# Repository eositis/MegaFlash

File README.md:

# MegaFlash for Apple IIc/IIc+

MegaFlash is an internal storage device for Apple IIc/IIc plus computer.

## Feature List

- 128MB/256MB Capacity, divided into 4/8 ProDOS Drives
- 256kB RAM Disk on Pico 2 (RP2350); 140kB on Pico W (RP2040)
- ROM Disk for Disaster Recovery
- 256kB Slinky Emulation on stock firmware
- Boot Menu (Similar to ROM4X/5X)
- Control Panel
- Real Time Clock with ProDOS clock driver
- Network Time Sync (NTP Client)
- Upload/Download ProDOS Image file via WIFI and TFTP Server
- Upload/Download ProDOS Image file via XModem and USB serial port
- FPU for Applesoft BASIC
- Bug fixes of System ROM and Applesoft

A brief [user guide](https://github.com/eositis/MegaFlash/blob/main/MegaFlash%20for%20a2s4000%20installation%20guide.pdf) is available for more information.

## Requirement
- Apple IIc computer with Memory Expansion Card connector or
- Apple IIc plus computer

System ROM replacement is required for MegaFlash to function.

## Hardware
The hardware is quite simple.  All the hard work is handled by Pi Pico.  Apple 65C02 CPU only needs to copy data between RAM and Pico. Schematic is available [here](./kicad/rev1.0/schematic-rev1.0.pdf).

- Raspberry Pi Pico2 W
- Winbond 25Q01 NOR Flash memory
- GAL16V8 PLD for address decode
- 5V to 3.3V Logic Level Shifter

## Project Directories

There are 3 software projects. There is not enough space in Apple ROM to store the Control Panel program.  The program is stored in Pico flash memory. 

`firmware` Project Directory of Apple ROM Patches\
`cpanel` Control Panel project\
`pico` Raspberry Pi Pico firmware\
`common` Common header files used by all 3 projects

## Sponsorship

MegaFlash development for commercial sale has been partly sponsored by PCBway. Preparing products for commercial release is expensive, often requiring board respins to resolve manufacturing and logistics issues. PCBway production and delivery are fast and efficient, helping compress the go-to market timeline. Many thanks!

<a href="https://www.pcbway.com">
  <p align="center">
  
</a>

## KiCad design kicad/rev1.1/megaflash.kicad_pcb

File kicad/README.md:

# MegaFlash PCB

Currently, there are two PCB revisions, 1.0 and 1.1. They are functionally identical. 

Rev 1.0 board is more compact. It is optimized for machine assembly.

Rev 1.1 board is bigger. It is designed for hand assembly.  The components are either through hole or 1.27mm pitch SOICs.

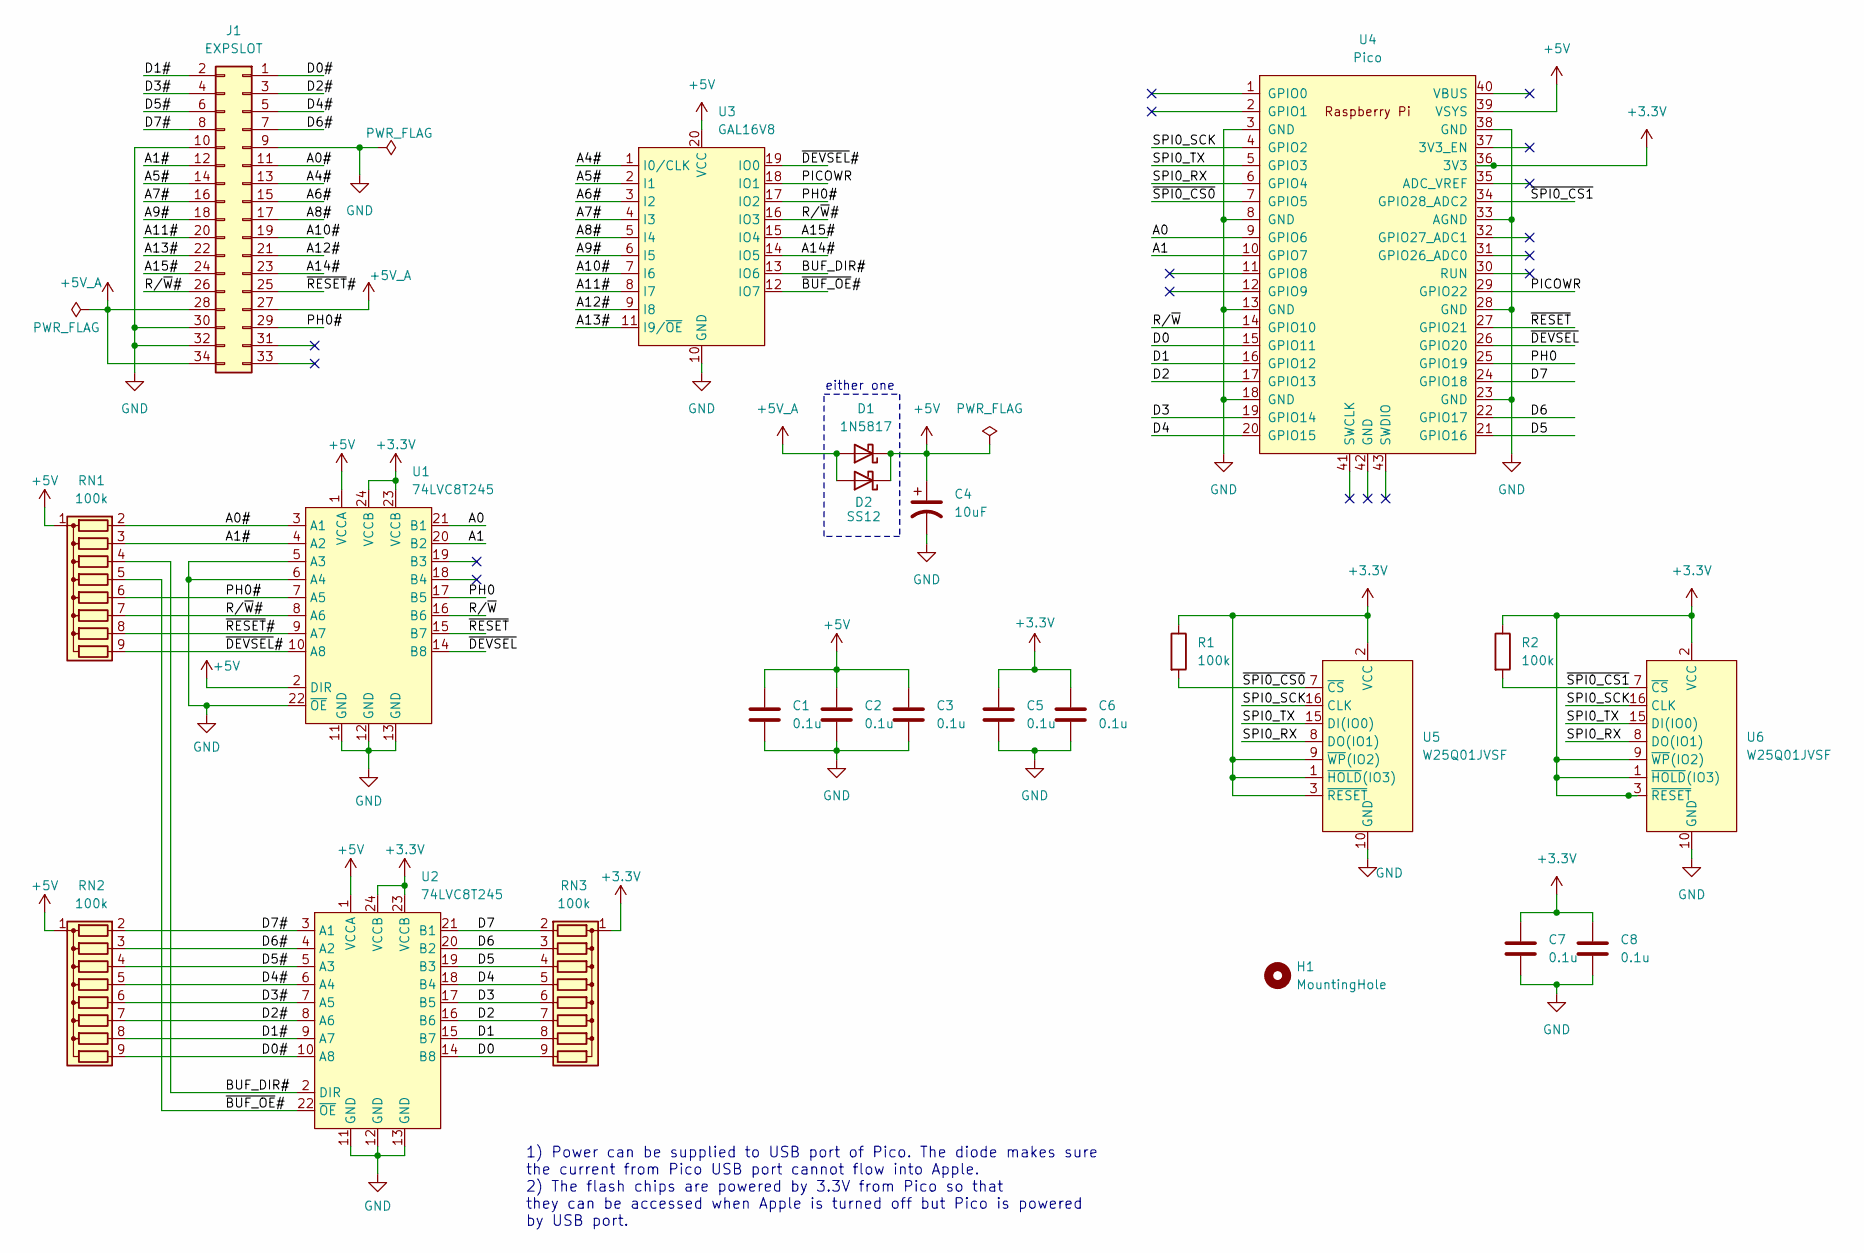
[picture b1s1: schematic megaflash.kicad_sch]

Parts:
C1, C2, C3, C5, C6, C7, C8: 0.1u; C_Disc_D5.1mm_W3.2mm_P5.00mm; Mouser Part No 594-K104K15X7RF5WH5
C4: 10uF; CP_Radial_D5.0mm_P2.00mm; Mouser Part No 710-860010372001
D1: 1N5817; D_DO-41_SOD81_P10.16mm_Horizontal; Mouser Part No 625-1N5817-E3/53
D2: SS12; D_SMA; Mouser Part No 625-SS12-E3
H1: MountingHole; MountingHole_2.7mm_M2.5
J1: EXPSLOT; PinHeader_2x17_P2.54mm_Vertical_Mirror; Mouser Part No 200-TSW11715GD
R1, R2: 100k; R_Axial_DIN0207_L6.3mm_D2.5mm_P10.16mm_Horizontal
RN1, RN2, RN3: 100k; R_Array_SIP9; Mouser Part No 652-4609X-1LF-100K
U1, U2: 74LVC8T245; SOIC-24W_7.5x15.4mm_P1.27mm; Mfr Part No SN74LVC8T245DWR; Mouser Part No 595-SN74LVC8T245DWR
U3: GAL16V8; DIP-20_W7.62mm_LongPads
U4: Pico; RPi_Pico_SMD_NO_LABEL_NO_DEBUG
U5, U6: W25Q01JVSF; SOIC-16W_7.5x10.3mm_P1.27mm; Mouser Part No 454-W25Q01JVSFIM

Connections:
+3.3V: C5.1, C6.1, C7.1, C8.1, R1.1, R2.1, RN3.1 (common), U1.23 (VCCB), U1.24 (VCCB), U2.23 (VCCB), U2.24 (VCCB), U4.36 (3V3), U5.1 (~HOLD(IO3)), U5.2 (VCC), U5.3 (~RESET), U5.9 (~WP(IO2)), U6.1 (~HOLD(IO3)), U6.2 (VCC), U6.3 (~RESET), U6.9 (~WP(IO2))
+5V: C1.1, C2.1, C3.1, C4.1, D1.1 (K), D2.1 (K), RN1.1 (common), RN2.1 (common), U1.1 (VCCA), U1.2 (DIR), U2.1 (VCCA), U3.20 (VCC), U4.39 (VSYS)
+5V_A: D1.2 (A), D2.2 (A), J1.27, J1.28, J1.34
/A0: U1.21 (B1), U4.9 (GPIO6)
/A0#: J1.11, RN1.2 (R1), U1.3 (A1)
/A1: U1.20 (B2), U4.10 (GPIO7)
/A1#: J1.12, RN1.3 (R2), U1.4 (A2)
/A4#: J1.13, U3.1 (I0/CLK)
/A5#: J1.14, U3.2 (I1)
/A6#: J1.15, U3.3 (I2)
/A7#: J1.16, U3.4 (I3)
/A8#: J1.17, U3.5 (I4)
/A9#: J1.18, U3.6 (I5)
/A10#: J1.19, U3.7 (I6)
/A11#: J1.20, U3.8 (I7)
/A12#: J1.21, U3.9 (I8)
/A13#: J1.22, U3.11 (I9/~OE)
/A14#: J1.23, U3.14 (IO5)
/A15#: J1.24, U3.15 (IO4)
/BUF_DIR#: RN1.4 (R3), U2.2 (DIR), U3.13 (IO6)
/D0: RN3.9 (R8), U2.14 (B8), U4.15 (GPIO11)
/D0#: J1.1, RN2.9 (R8), U2.10 (A8)
/D1: RN3.8 (R7), U2.15 (B7), U4.16 (GPIO12)
/D1#: J1.2, RN2.8 (R7), U2.9 (A7)
/D2: RN3.7 (R6), U2.16 (B6), U4.17 (GPIO13)
/D2#: J1.3, RN2.7 (R6), U2.8 (A6)
/D3: RN3.6 (R5), U2.17 (B5), U4.19 (GPIO14)
/D3#: J1.4, RN2.6 (R5), U2.7 (A5)
/D4: RN3.5 (R4), U2.18 (B4), U4.20 (GPIO15)
/D4#: J1.5, RN2.5 (R4), U2.6 (A4)
/D5: RN3.4 (R3), U2.19 (B3), U4.21 (GPIO16)
/D5#: J1.6, RN2.4 (R3), U2.5 (A3)
/D6: RN3.3 (R2), U2.20 (B2), U4.22 (GPIO17)
/D6#: J1.7, RN2.3 (R2), U2.4 (A2)
/D7: RN3.2 (R1), U2.21 (B1), U4.24 (GPIO18)
/D7#: J1.8, RN2.2 (R1), U2.3 (A1)
/PH0: U1.17 (B5), U4.25 (GPIO19)
/PH0#: J1.29, RN1.6 (R5), U1.7 (A5), U3.17 (IO2)
/PICOWR: U3.18 (IO1), U4.29 (GPIO22)
/R/~W: U1.16 (B6), U4.14 (GPIO10)
/R/~W#: J1.26, RN1.7 (R6), U1.8 (A6), U3.16 (IO3)
/SPI0_RX: U4.6 (GPIO4), U5.8 (DO(IO1)), U6.8 (DO(IO1))
/SPI0_SCK: U4.4 (GPIO2), U5.16 (CLK), U6.16 (CLK)
/SPI0_TX: U4.5 (GPIO3), U5.15 (DI(IO0)), U6.15 (DI(IO0))
/~BUF_OE#: RN1.5 (R4), U2.22 (~OE), U3.12 (IO7)
/~DEVSEL: U1.14 (B8), U4.26 (GPIO20)
/~DEVSEL#: RN1.9 (R8), U1.10 (A8), U3.19 (IO0)
/~RESET: U1.15 (B7), U4.27 (GPIO21)
/~RESET#: J1.25, RN1.8 (R7), U1.9 (A7)
/~SPI0_CS0: R1.2, U4.7 (GPIO5), U5.7 (~CS)
/~SPI0_CS1: R2.2, U4.34 (GPIO28_ADC2), U6.7 (~CS)
GND: C1.2, C2.2, C3.2, C4.2, C5.2, C6.2, C7.2, C8.2, J1.9, J1.10, J1.30, J1.32, U1.5 (A3), U1.6 (A4), U1.11 (GND), U1.12 (GND), U1.13 (GND), U1.22 (~OE), U2.11 (GND), U2.12 (GND), U2.13 (GND), U3.10 (GND), U4.3 (GND), U4.8 (GND), U4.13 (GND), U4.18 (GND), U4.23 (GND), U4.28 (GND), U4.33 (AGND), U4.38 (GND), U5.10 (GND), U6.10 (GND)

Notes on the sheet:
1) Power can be supplied to USB port of Pico. The diode makes sure the current from Pico USB port cannot flow into Apple. 2) The flash chips are powered by 3.3V from Pico so that they can be accessed when Apple is turned off but Pico is powered by USB port.
either one

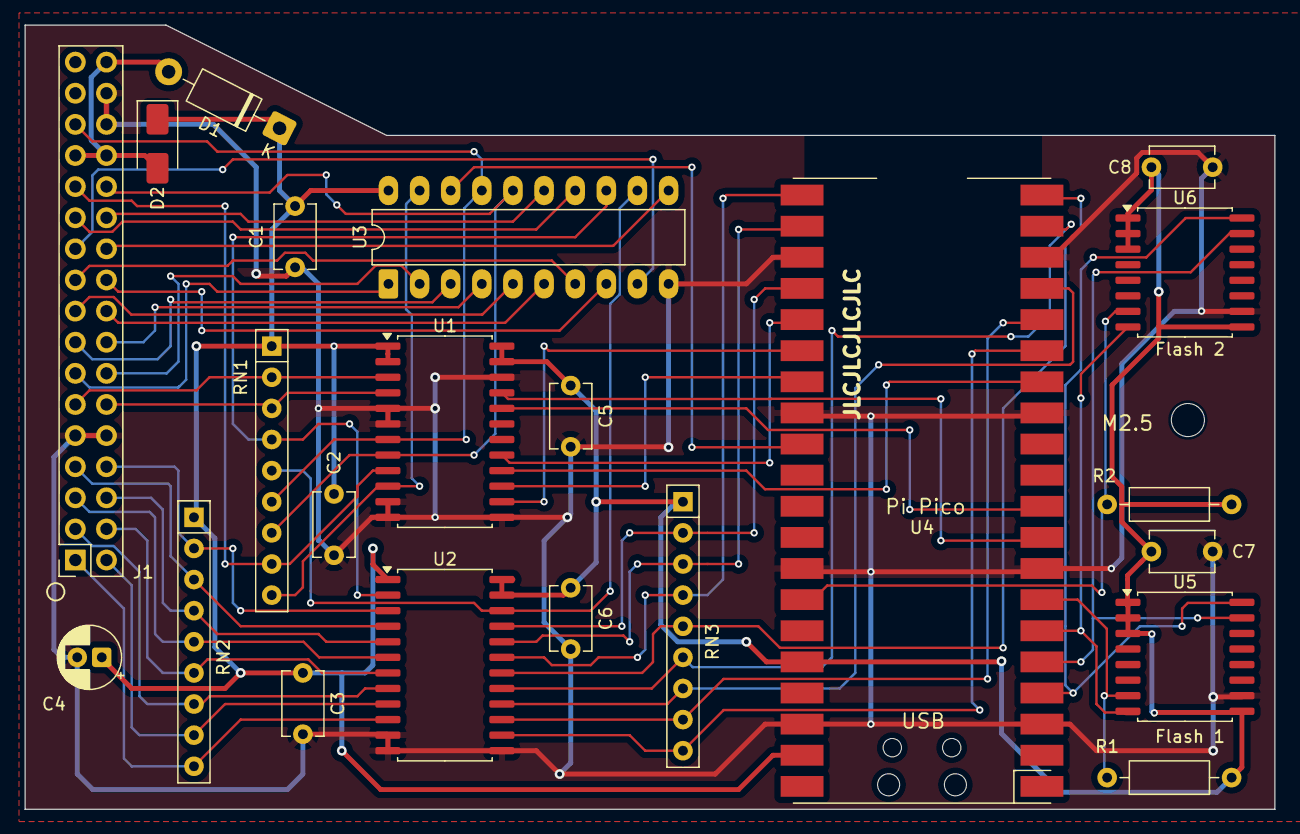
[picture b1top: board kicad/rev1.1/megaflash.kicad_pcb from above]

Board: 2 copper layers, 102.0 x 64.0 mm, 23 parts (0 on the bottom side), 52 nets.

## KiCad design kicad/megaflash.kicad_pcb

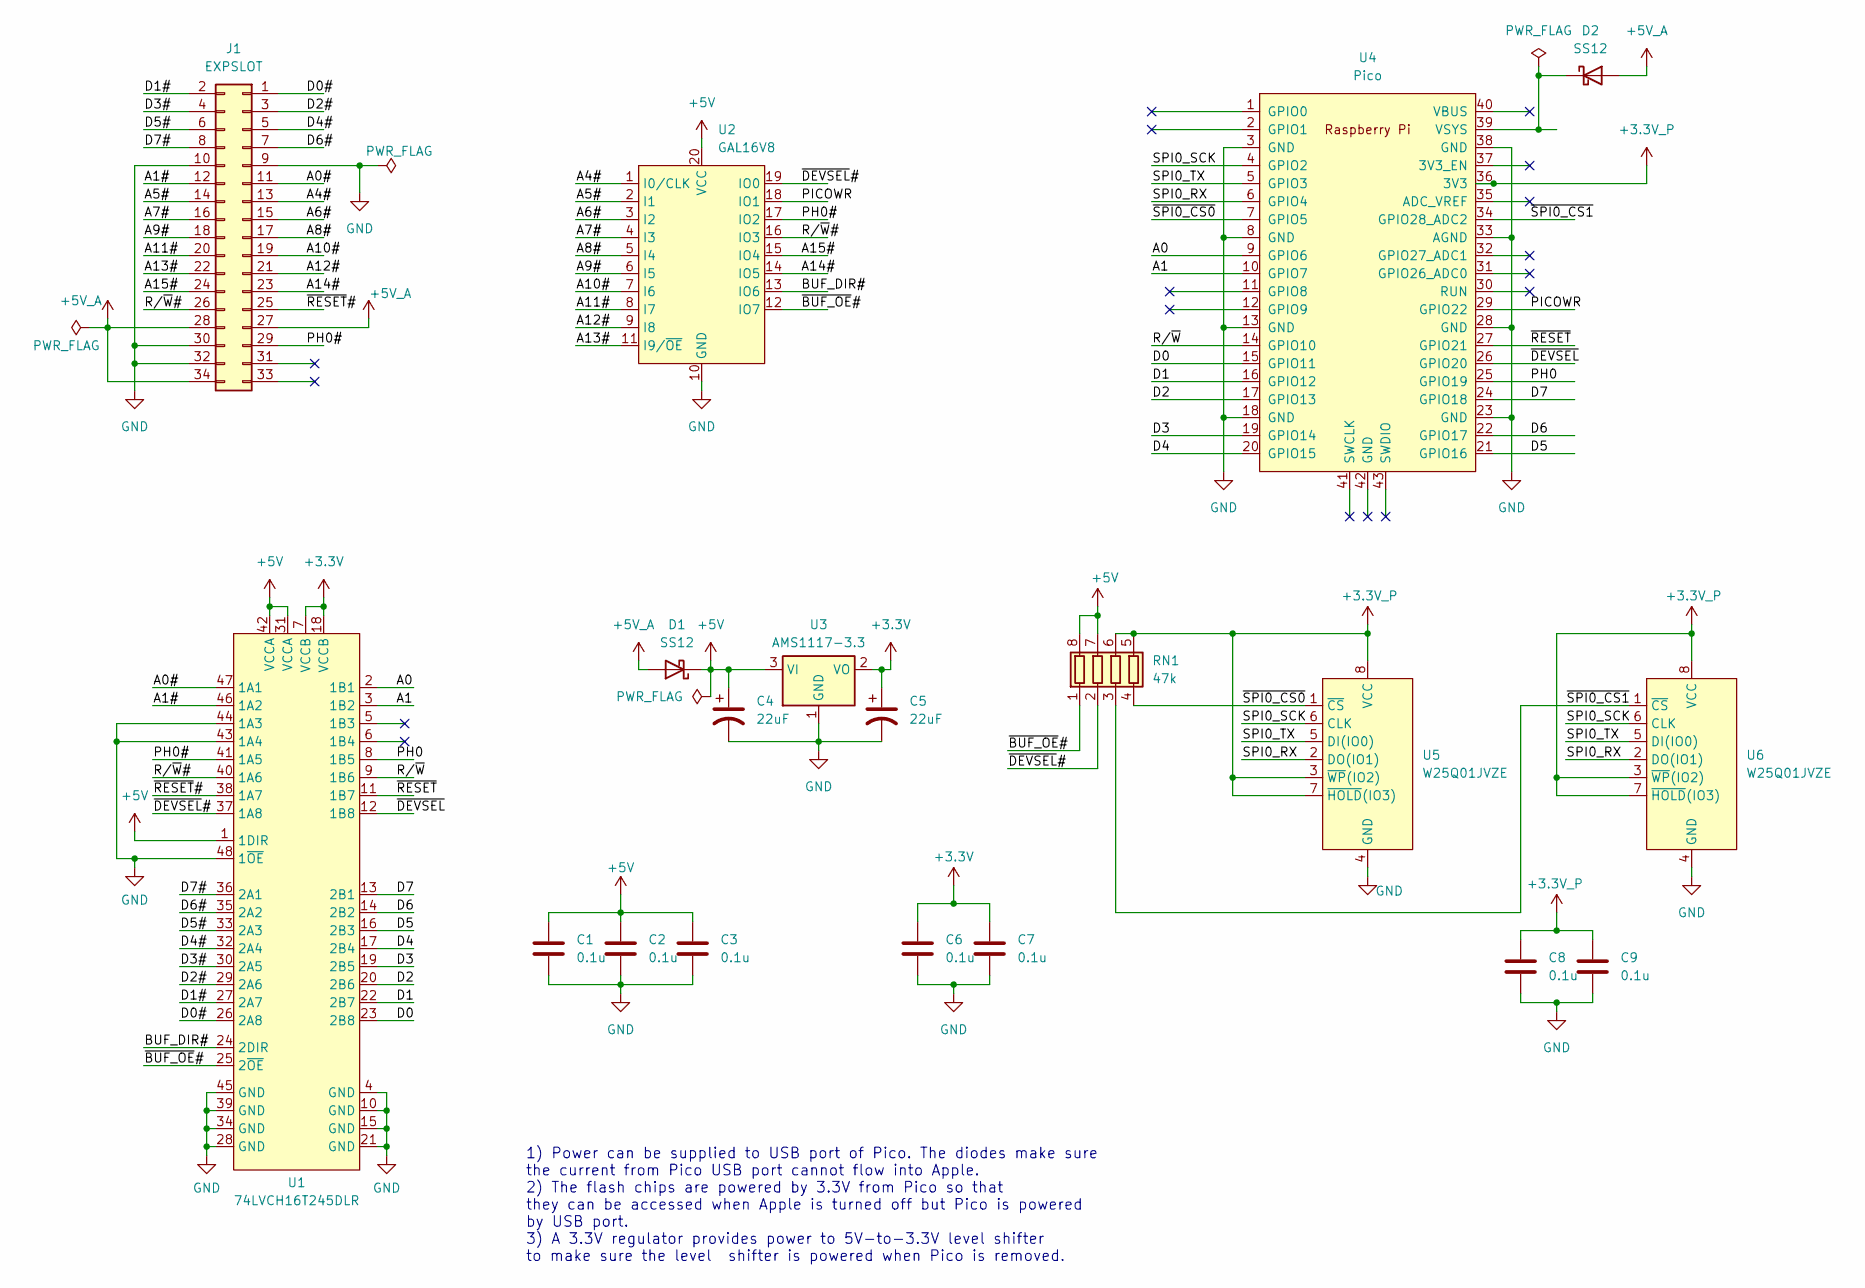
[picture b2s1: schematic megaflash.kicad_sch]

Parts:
C1, C2, C3, C6, C7, C8, C9: 0.1u; C_0805_2012Metric_Pad1.18x1.45mm_HandSolder
C4, C5: 22uF; CP_EIA-3528-12_Kemet-T; Mouser Part No 80-T491B226K010
D1, D2: SS12; D_SMA; Mouser Part No 625-SS12-E3
J1: EXPSLOT; PinHeader_2x17_P2.54mm_Vertical_Mirror; Mouser Part No 200-TSW11715GD
RN1: 47k; R_Array_Convex_4x0603
U1: 74LVCH16T245DLR; SSOP-48_7.5x15.9mm_P0.635mm; Mouser Part No 595-SN74LVCH16T245LR
U2: GAL16V8; PLCC-20_SMD-Socket
U3: AMS1117-3.3; SOT-223-3_TabPin2
U4: Pico; RPi_Pico_SMD_NO_LABEL_NO_DEBUG
U5, U6: W25Q01JVZE; WSON-8-1EP_8x6mm_P1.27mm_EP3.4x4.3mm; Mouser Part No 454-W25Q01JVZEIMTU

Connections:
+3.3V: C5.1, C6.1, C7.1, U1.7 (VCCB), U1.18 (VCCB), U3.2 (VO)
+3.3V_P: C8.1, C9.1, RN1.5 (R4.2), RN1.6 (R3.2), U4.36 (3V3), U5.3 (~WP(IO2)), U5.7 (~HOLD(IO3)), U5.8 (VCC), U6.3 (~WP(IO2)), U6.7 (~HOLD(IO3)), U6.8 (VCC)
+5V: C1.1, C2.1, C3.1, C4.1, D1.1 (K), RN1.7 (R2.2), RN1.8 (R1.2), U1.1 (1DIR), U1.31 (VCCA), U1.42 (VCCA), U2.20 (VCC), U3.3 (VI)
+5V_A: D1.2 (A), D2.2 (A), J1.27, J1.28, J1.34
/A0: U1.2 (1B1), U4.9 (GPIO6)
/A0#: J1.11, U1.47 (1A1)
/A1: U1.3 (1B2), U4.10 (GPIO7)
/A1#: J1.12, U1.46 (1A2)
/A4#: J1.13, U2.1 (I0/CLK)
/A5#: J1.14, U2.2 (I1)
/A6#: J1.15, U2.3 (I2)
/A7#: J1.16, U2.4 (I3)
/A8#: J1.17, U2.5 (I4)
/A9#: J1.18, U2.6 (I5)
/A10#: J1.19, U2.7 (I6)
/A11#: J1.20, U2.8 (I7)
/A12#: J1.21, U2.9 (I8)
/A13#: J1.22, U2.11 (I9/~OE)
/A14#: J1.23, U2.14 (IO5)
/A15#: J1.24, U2.15 (IO4)
/BUF_DIR#: U1.24 (2DIR), U2.13 (IO6)
/D0: U1.23 (2B8), U4.15 (GPIO11)
/D0#: J1.1, U1.26 (2A8)
/D1: U1.22 (2B7), U4.16 (GPIO12)
/D1#: J1.2, U1.27 (2A7)
/D2: U1.20 (2B6), U4.17 (GPIO13)
/D2#: J1.3, U1.29 (2A6)
/D3: U1.19 (2B5), U4.19 (GPIO14)
/D3#: J1.4, U1.30 (2A5)
/D4: U1.17 (2B4), U4.20 (GPIO15)
/D4#: J1.5, U1.32 (2A4)
/D5: U1.16 (2B3), U4.21 (GPIO16)
/D5#: J1.6, U1.33 (2A3)
/D6: U1.14 (2B2), U4.22 (GPIO17)
/D6#: J1.7, U1.35 (2A2)
/D7: U1.13 (2B1), U4.24 (GPIO18)
/D7#: J1.8, U1.36 (2A1)
/PH0: U1.8 (1B5), U4.25 (GPIO19)
/PH0#: J1.29, U1.41 (1A5), U2.17 (IO2)
/PICOWR: U2.18 (IO1), U4.29 (GPIO22)
/R/~W: U1.9 (1B6), U4.14 (GPIO10)
/R/~W#: J1.26, U1.40 (1A6), U2.16 (IO3)
/SPI0_RX: U4.6 (GPIO4), U5.2 (DO(IO1)), U6.2 (DO(IO1))
/SPI0_SCK: U4.4 (GPIO2), U5.6 (CLK), U6.6 (CLK)
/SPI0_TX: U4.5 (GPIO3), U5.5 (DI(IO0)), U6.5 (DI(IO0))
/~BUF_OE#: RN1.1 (R1.1), U1.25 (2~OE), U2.12 (IO7)
/~DEVSEL: U1.12 (1B8), U4.26 (GPIO20)
/~DEVSEL#: RN1.2 (R2.1), U1.37 (1A8), U2.19 (IO0)
/~RESET: U1.11 (1B7), U4.27 (GPIO21)
/~RESET#: J1.25, U1.38 (1A7)
/~SPI0_CS0: RN1.4 (R4.1), U4.7 (GPIO5), U5.1 (~CS)
/~SPI0_CS1: RN1.3 (R3.1), U4.34 (GPIO28_ADC2), U6.1 (~CS)
GND: C1.2, C2.2, C3.2, C4.2, C5.2, C6.2, C7.2, C8.2, C9.2, J1.9, J1.10, J1.30, J1.32, U1.4 (GND), U1.10 (GND), U1.15 (GND), U1.21 (GND), U1.28 (GND), U1.34 (GND), U1.39 (GND), U1.43 (1A4), U1.44 (1A3), U1.45 (GND), U1.48 (1~OE), U2.10 (GND), U3.1 (GND), U4.3 (GND), U4.8 (GND), U4.13 (GND), U4.18 (GND), U4.23 (GND), U4.28 (GND), U4.33 (AGND), U4.38 (GND), U5.4 (GND), U6.4 (GND)
unnamed: D2.1 (K), U4.39 (VSYS)

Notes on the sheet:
1) Power can be supplied to USB port of Pico. The diodes make sure the current from Pico USB port cannot flow into Apple. 2) The flash chips are powered by 3.3V from Pico so that they can be accessed when Apple is turned off but Pico is powered by USB port. 3) A 3.3V regulator provides power to 5V-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

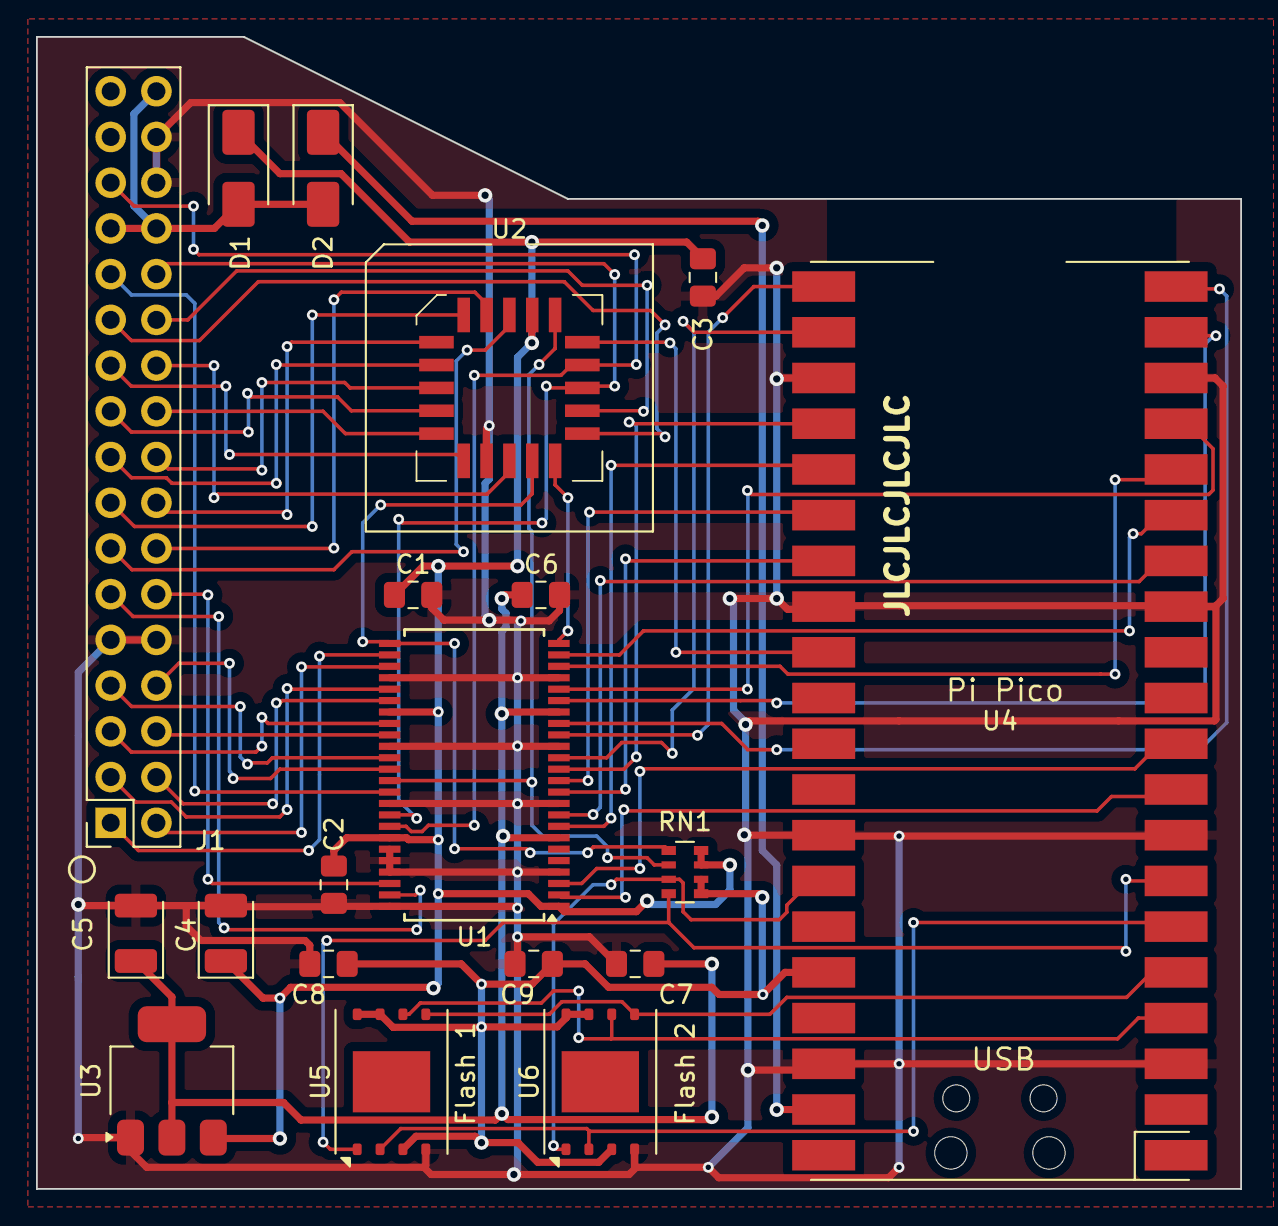
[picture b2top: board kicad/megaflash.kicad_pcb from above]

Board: 2 copper layers, 66.9 x 64.0 mm, 19 parts (0 on the bottom side), 54 nets.

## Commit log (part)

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2025-08-17 Updated prompt message
2025-08-17 Corrected Typos
2025-08-19 Version 1.1.4
2025-08-25 Version 1.1.5
2025-09-05 PCB Rev 1.1A images
2025-09-05 Added Rev1.1A PCB
2025-09-05 Corrected filename
2025-09-05 Removed Rev1.1a PCB
2025-09-05 Revised Rev1.1b PCB
2025-09-06 Revised PCB Rev 1.1B
2025-09-07 Rev 1.0A image
2025-09-07 Updated schematic
2025-09-10 Ver 1.1.6
2025-09-13 Added PCB Assembly Notes
2025-09-18 Updated comment
2025-09-18 Refactor flash access routines to hide implementation details
2025-09-19 Mutex Lock in exported functions only
2025-09-19 Ramdisk has its own dedicated DMA channel
2025-09-19 Removed unnecessary DMA access
2025-09-19 Reduced memory usage
2025-09-20 Updated user guide
2025-09-20 Updated prompt messages
2025-09-20 Updated comments
2025-09-20 Corrected comments
2026-02-06 Corrected comment
2026-02-06 Corrected code formatting
2026-02-07 enabling romdisk
    update to enable romdisk to always be published
2026-02-20 Code Cleanup
2026-02-21 Removed unused constants
2026-02-21 Added static keyword
2026-02-21 Added status keyword
2026-02-22 Updated userguide.pdf
2026-02-22 Reduced memory usage in SLOTROM segment
2026-02-22 jmp to boot menu via swjmp routine
2026-02-22 Optimized data transfer routines
2026-02-22 Saved 3 bytes of ROM space
2026-02-24 Optimized the speed of data transfer routine
2026-02-24 Updated loadcpanel routine
2026-02-24 Changed firmware version to 1.0.1
2026-02-24 Moved dispatch routine to ROM1 segment
2026-02-24 Removed unused code
2026-02-24 Optimized p8spentry routine
2026-02-24 Replaced > and < operators with .HIBYTE and .LOBYTE
2026-02-24 Updted comment
2026-02-25 Made use of free space in - of Aux ROM bank
2026-02-25 Rearranged segment allocation
2026-02-25 Updated speed test results
2026-02-26 Corrected the description of SPI mode
2026-02-27 Added CMD_FSUB command
2026-02-27 Renamed variable
2026-03-01 Auto adjust PIO clock divider from clk_sys
2026-03-01 Clean up slinky.c source code
2026-03-02 Source code cleanup
2026-03-02 Removed IRQ0 from RP2350 pio
2026-03-03 Renamed Timer commands to Stopwatch
2026-03-03 Adjusted loop count from clk_sys
2026-03-03 Removed unused #include
2026-03-03 Removed __no_inline_not_in_flash_func from some functions
2026-03-04 Applied inline selectively
2026-03-04 Moved definition of union registers from a2bus.c to busloop.c
2026-03-05 Optimized DMA routines
2026-03-05 Added comment
2026-03-05 Optimized LoadFAC and LoadARG routines
2026-03-06 Optimized StoreResult routine
2026-03-06 Formatting
2026-03-06 Reduced code size
2026-03-06 Reduced sleep duration
2026-03-06 Assigned FPU segment to address
2026-03-07 Added fswrts routine to improve performance on IIc+
2026-03-07 Added .DS_Store to .gitignore
2026-03-07 Moved portion of slxeq2 routine to ROM1 for better performance on IIc+
2026-03-07 Enabled CPU overclocking
2026-03-07 Clean up Makefile
2026-03-07 c0c4 fixes
2026-03-08 Set CYW43 PIO clock divider if CPU is overclocked
2026-03-08 v1.1.9eo
    romdisk should show up in the disk selector
    devsel and a0-a3 pulls disabled
2026-03-09 reduced udp timing loop from 50m to 10ms
    this change should improve TFTP performance
2026-03-09 1.1.11-eo tftp rx buffering
    ## TFTP RX: buffer incoming traffic during flash write
    - **Incoming TFTP DATA buffering:** While the TFTP RX task is blocked in flash write (especially during the ~220–250 ms sector erase every 16 blocks), incoming DATA packets are now received and queue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
    - **Flash yield callback:** The flash layer calls an optional yield callback (~1 ms) during `WaitUntilBusyClear()`. TFTP RX registers `tftp_network_yield()` so `cyw43_arch_poll()` runs during erase a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
    - **RX queue:** Up to 16 DATA packets are stored in a circular queue when they arrive during a blocking write. The event loop drains one
2026-03-09 V1.1.13-eo
    # V1.1.13-eo
    ## UDP/TFTP heartbeat reverted to 50 ms
    - **HEARTBEAT_PERIOD:** Reverted from 10 ms back to 50 ms in `udptask.h`. The shorter period caused TFTP upload timeouts and crashes (lwIP re-entrancy risk).
    - **TFTP RX buffering** (V1.1.11) remains: incoming DATA packets are queued during flash erase, so the 50 ms loop is sufficient for most transfers.
    ## Control Panel: ROM Disk row in Drives Enable
    - **ROM Disk visibility:** The ROM Disk checkbox row was not shown because it overwrote the last drive row. Fixed: ROM Disk row is now at `YPOS+unitCount+1`; drive checkboxes use `YPOS+i`. ROM Disk a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
2026-03-09 V1.1.15-eo
    @ -0,0 +1,19 @@
    # V1.1.15-eo
    ## WiFi kept online between sessions
    - **No teardown on session end:** The CUDPTask destructor no longer disconnects or deinitializes WiFi when a TFTP/NTP/TestWifi session completes. Only the UDP PCB and RX buffer are freed; CYW43 and t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
    - **Fast restart:** Subsequent TFTP/NTP sessions skip InitCyw43 (static guard) and ConnectWifi returns immediately when already LINK_UP. TFTP starts much faster when run again soon after a previous s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
    - **TFTP receive fix (reuse path):** When reusing WiFi, ConnectWifi now runs a ~100 ms warmup (100× `cyw43_arch_poll()` + 1 ms) before returning. This stabilizes lwIP/CYW43 so the new UDP PCB
2026-03-09 Increase core voltage to 1.15V when overclock
2026-03-11 additional documentation and C libraries
2026-03-11 Moved CPU overclock build flag to CMakeLists.txt
2026-03-11 V1.1.18-eo
    @ -0,0 +1,20 @@
    # V1.1.18-eo
    ## WiFi kept online between sessions
    - **No teardown on session end:** The CUDPTask destructor no longer disconnects or deinitializes WiFi when a TFTP/NTP/TestWifi session completes. Only the UDP PCB and RX buffer are freed; CYW43 and t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
    - **Fast restart:** Subsequent TFTP/NTP sessions skip InitCyw43 (static guard) and ConnectWifi returns immediately when already LINK_UP. TFTP starts much faster when run again soon after a previous s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
    - **TFTP receive fix (reuse path):** When reusing WiFi, ConnectWifi now runs a ~100 ms warmup (100× `cyw43_arch_poll()` + 1 ms) before returning. This stabilizes lwIP/CYW43 so the new UDP PCB
2026-03-14 Fix: NTP is updated twice when power on
2026-03-14 Call EvtUDPReceived() from udp_callback()
2026-03-14 Avoid race condition with TFTP server
2026-03-15 Added const keyword
2026-03-15 TFTP Download with DOS order image support
2026-03-16 Changed menu position
2026-03-17 C library updates
2026-03-17 Updated for V1.1.9
2026-03-17 Call EvtUDPReceived() from CUDPTask::Run() instead of udp_callback()
2026-03-17 Updated version number
2026-03-17 Added cyw43_arch_lwip_begin()/_end()
2026-03-17 Added helper class CInterrupt
2026-03-17 Renamed udp_callback() to udp_recv_callback()
2026-03-18 V1.1.19-eo
    starting rebuild of wifi loop
2026-03-18 V1.1.20-eo
    Network manager now handling all of the legacy IP traffic. Ready to add UthernetII emulation
2026-03-18 Renamed method name to ValidateBlockNumber()
2026-03-18 Renamed CInterrupt to CInterruptDisabler
2026-03-19 V1.1.10
2026-03-21 V1.1.24-eo
    branching 1.1.x here. this will be the last 1.1.x feature release.
    This release has control panel UI fixes and re-enabled USB console when independent of the Apple II.
2026-03-24 Added CLAMP macro
2026-03-25 Managed task pointer with std::unique_ptr
2026-03-26 Added override keyword
2026-03-27 Device Info shows GCC Version
2026-03-27 V1.1.x: DNS race fix, RAM disk size, TFTP heap diagnostics, U2/pump updates
    Register DNS pending owner before dns_gethostbyname so fast lwIP callbacks
    are not dropped (intermittent DNS timeouts). Reduce RP2350 RAMDISK_SIZE to
    256 KiB to free SRAM for heap and network stacks. Add DebugPrintHeapState
    before TFTP allocation; document TFTP OOM and DNS ordering in implementation
    notes.
    Includes NetworkPump session work, uthernet2_net.cpp (replaces .c), U2 monitor,
2026-03-27 Session log: document 1.2.x branch (parallel to main, V1.2.0 line)
    Made-with: Cursor
2026-03-30 Fix image link and update user guide reference
    Updated image link and user guide path in README.
2026-04-03 Port Thomas storage: RAM disk DMA, ROM memcpy, flash read DMA timeout
    - ramdisk: dedicated DMA channel + InitRamdisk() after InitDMAChannel
    - romdisk: CPU memcpy for reads; keep romdiskFirst / fork defaults
    - flash: ReadFromFlashByDMA timeout/abort + CRC32Aligned fallback in
    tsReadOneBlock/tsReadSector (overclock/TFTP hang mitigation)
    - Docs: SESSION_LOG, Implementation-notes §4e
    Made-with: Cursor
2026-04-05 Removed excess blank lines
2026-04-05 Text Formatting
2026-04-06 Port Thomas smartport.s: HOMESEGMENT, ZP restore loops
    - .define HOMESEGMENT ROM1; use for main SmartPort code segments
    - RESTOREZPSCRATCH: indexed sta z:zpscratch+ZPSCRATCHSIZE,x + bne loop
    - ZPSIZE restore: blt -> bne (same count)
    - Drop obsolete IIc+ debug segment comment block
    - Docs: SESSION_LOG, Implementation-notes §4g
    Made-with: Cursor
2026-04-06 fswrts + swjmp_ay for ZIP/IIc+ ROM bank return (Thomas)
    - patches: FB19 jmp slxeq; B1_FFC8 sta rombank (fswrts); export fswrts
    - megaflash: cold exit via ($0000)-1 + swjmp_ay; boot menu via BMRUN-1
    - macros: ld16iay
    - iic/iicplus + merge configs: B1_FFC8 fragment
    - Docs: SESSION_LOG, impl notes §4h, upstream comparison table
    Made-with: Cursor
2026-04-06 ported Thomas' impprovements, adding flash testing utility
2026-04-06 Added Alliance AS25F3512MQ flash support
2026-04-06 Add overnight FLASHSOAK validator with CSV and TFTP loop
    Add a destructive long-run Applesoft soak tool that formats writable units, exercises file churn, round-trips images through TFTP, and verifies whole-volume checksums while logging CSV events for lat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
    Made-with: Cursor
2026-04-07 flash: Alliance JEDEC 0x204020 — mask RDID, explicit 512 Mbit match
    - tsReadJEDECID: 24-bit mask + uint32_t shifts for clean JEDEC assembly
    - ChipIDToCapacity: jedec24 + explicit 0x204020 (Thomas); type_cap unchanged
    - Docs §16 + SESSION_LOG
    Made-with: Cursor
2026-04-08 Add sponsorship information for MegaFlash project
    Add sponsorship section highlighting PCBway's support for MegaFlash development.
2026-04-25 Replaced std::queue with a ring buffer
2026-04-25 Updated version info
2026-04-25 When 6502 reads status register, the request is not forwared to the CPU.
2026-04-26 Fix: TFTP failed to restart when blksize option from server is invalid.
2026-04-26 Text formattting
2026-04-28 Experimental ISSI Flash chip support
2026-05-17 Revision 1.2 PCB
2026-05-24 Uthernet work continues.
    Uthernet updates
    documentation update
2026-05-26 Add files via upload
    userguilde grammar fixes
2026-06-11 documentation update
2026-06-12 Slot number is configurable.
2026-06-24 improved network performance
2026-06-25 debug build: pico/build-debug.sh
    HEAD=d74bd51 branch=main tree=dirty
    host=Darwin 25.5.0 arm64
    target=pico2_debug board=pico2_w (configure CMake cache for U2_* / FIRMWARE_BUILD_TIMESTAMP)
2026-06-25 debug build: pico/build-debug.sh
    HEAD=25eb1c5 branch=main tree=dirty
    host=Darwin 25.5.0 arm64
    target=pico2_debug board=pico2_w (configure CMake cache for U2_* / FIRMWARE_BUILD_TIMESTAMP)
2026-06-25 debug build: pico/build-debug.sh
    HEAD=d2d40e4 branch=main tree=dirty
    host=Darwin 25.5.0 arm64
    target=pico2_debug board=pico2_w (configure CMake cache for U2_* / FIRMWARE_BUILD_TIMESTAMP)
2026-06-25 debug build: pico/build-debug.sh
    HEAD=0088fc0 branch=main tree=dirty
    host=Darwin 25.5.0 arm64
    target=pico2_debug board=pico2_w (configure CMake cache for U2_* / FIRMWARE_BUILD_TIMESTAMP)
2026-06-27 debug build: pico/build-debug.sh
    HEAD=b5e4190 branch=main tree=dirty
    host=Darwin 25.5.0 arm64
    target=pico2_debug board=pico2_w (configure CMake cache for U2_* / FIRMWARE_BUILD_TIMESTAMP)
